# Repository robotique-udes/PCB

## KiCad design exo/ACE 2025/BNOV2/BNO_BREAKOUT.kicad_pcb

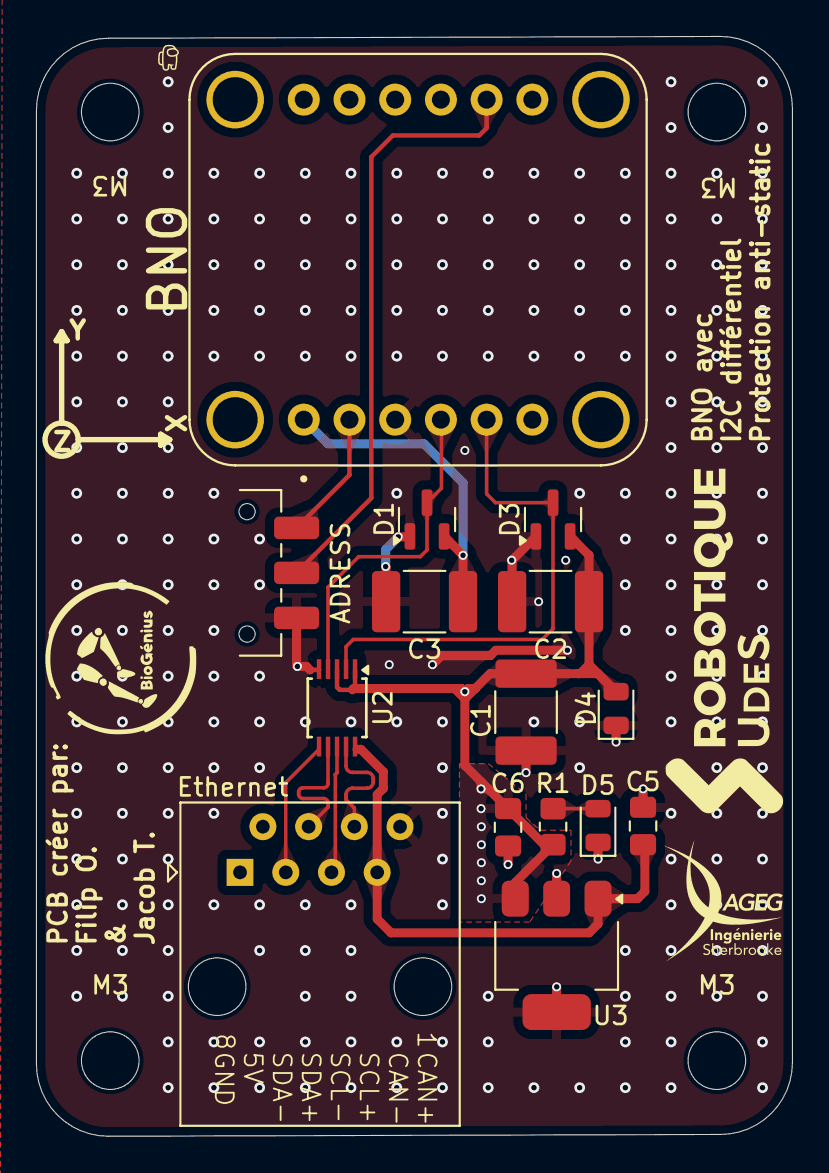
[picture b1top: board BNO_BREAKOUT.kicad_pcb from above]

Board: 2 copper layers, 42.0 x 61.1 mm, 17 parts (0 on the bottom side), 12 nets.

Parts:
ADRESS: SW_SPDT; SW_SPDT_CK_JS102011SAQN
BNO: 4754; MODULE_4754
C1: 4.7uF; C_1812_4532Metric_Pad1.57x3.40mm_HandSolder
C2, C3: 1n; C_1812_4532Metric_Pad1.57x3.40mm_HandSolder
C5, C6: 4,7µF; C_0805_2012Metric_Pad1.18x1.45mm_HandSolder
D1, D3: BAV99; SOT-23
D4: D_TVS_Filled; D_0805_2012Metric
D5: Green_power; D_0805_2012Metric
Ethernet: RJ45; RJ45_Amphenol_54602-x08_Horizontal
M3, M3#2: MountingHole_3.2mm_M3
R1: 330; R_0805_2012Metric_Pad1.20x1.40mm_HandSolder
U2: PCA9615DPZ; TSSOP-10_3x3mm_P0.5mm
U3: AP7361C-33E; SOT-223-3_TabPin2

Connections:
/3V3: BNO.JP1_1 (VIN), C1.1, C2.1, C3.1, C6.2, D1.2 (A), D3.2 (A), D4.2 (A2), R1.1, U2.1 (VDD(A)), U2.3 (EN), U3.3 (VO)
/5V: C5.2, Ethernet.7, U2.10 (VDD(B)), U3.1 (VI)
/SCL: BNO.JP1_4 (SCL), D1.3 (K), U2.4 (SCL)
/SCL+: Ethernet.3, U2.6 (DSCLM)
/SCL-: Ethernet.4, U2.7 (DSCLP)
/SDA: BNO.JP1_5 (SDA), D3.3 (K), U2.2 (SDA)
/SDA+: Ethernet.5, U2.8 (DSDAP)
/SDA-: Ethernet.6, U2.9 (DSDAM)
GND: ADRESS.3 (C), BNO.JP1_3 (GND), C1.2, C2.2, C3.2, C5.1, C6.1, D1.1 (K), D3.1 (K), D4.1 (A1), D5.1 (K), Ethernet.8, U2.5 (VSS), U3.2 (GND)
unnamed: D5.2 (A), R1.2
unnamed: ADRESS.1 (A), BNO.JP1_2 (3VO)
unnamed: ADRESS.2 (B), BNO.JP2_5 (DI)

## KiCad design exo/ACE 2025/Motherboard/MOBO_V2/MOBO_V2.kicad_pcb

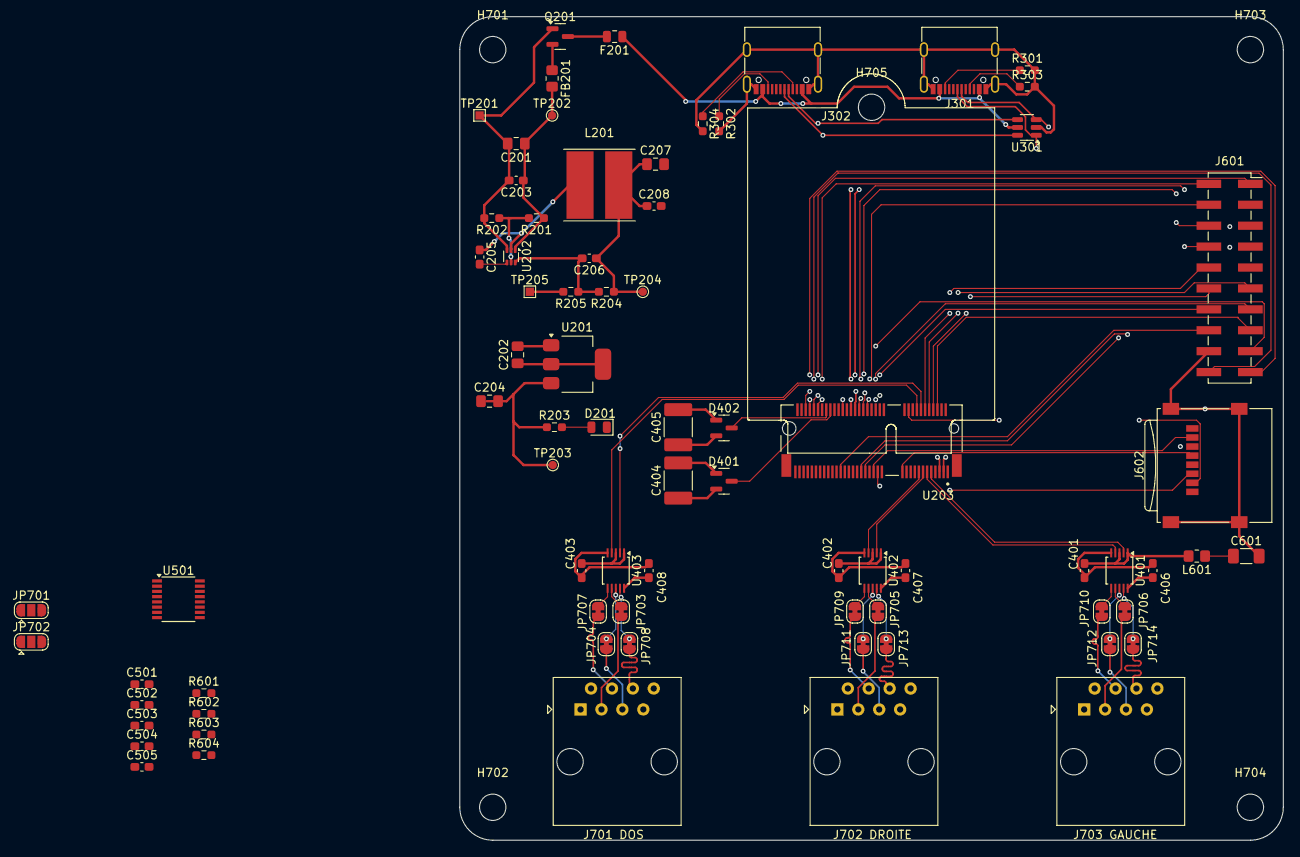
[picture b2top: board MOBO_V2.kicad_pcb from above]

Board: 4 copper layers, 100.0 x 100.0 mm, 82 parts (0 on the bottom side), 89 nets.

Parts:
C201: 10µF; C_0805_2012Metric_Pad1.18x1.45mm_HandSolder
C202, C204: 4,7µF; C_0805_2012Metric_Pad1.18x1.45mm_HandSolder
C203, C205, C208: 0,1µF; C_0603_1608Metric_Pad1.08x0.95mm_HandSolder
C206: 33pF; C_0603_1608Metric_Pad1.08x0.95mm_HandSolder
C207: 22µF; C_0805_2012Metric_Pad1.18x1.45mm_HandSolder
C401, C402, C403, C406, C407, C408: 1nF; C_0603_1608Metric_Pad1.08x0.95mm_HandSolder
C404, C405: 1n; C_1812_4532Metric_Pad1.57x3.40mm_HandSolder
C501, C502, C503, C504, C505: 0.1µF; C_0603_1608Metric_Pad1.08x0.95mm_HandSolder
C601: 47µF; C_1206_3216Metric_Pad1.33x1.80mm_HandSolder
D201: Green_power; D_0805_2012Metric
D401, D402: BAV99; SOT-23
F201: SMD0805B110TF; Fuse_0805_2012Metric
FB201: 600 @ 100MHz; R_0805_2012Metric_Pad1.20x1.40mm_HandSolder
H701, H702, H703, H704: MountingHole; MountingHole_3.2mm_M3
H705: MountingHole SoM; MountingHole_3.2mm_M3
J301: USB_C_UART; USB_C_Receptacle_G-Switch_GT-USB-7010ASV
J302: USB_C_DEBUG; USB_C_Receptacle_G-Switch_GT-USB-7010ASV
J601: Conn_02x10_Counter_Clockwise; PinSocket_2x10_P2.54mm_Vertical_SMD
J602: Micro_SD_Card; microSD_HC_Wuerth_693072010801
J701 DOS, J702 DROITE, J703 GAUCHE: RJ45; RJ45_Amphenol_54602-x08_Horizontal
JP701, JP702: SolderJumper_3_Open; SolderJumper-3_P1.3mm_Open_RoundedPad1.0x1.5mm
JP703, JP704, JP705, JP706, JP707, JP708, JP709, JP710, JP711, JP712, JP713, JP714: SolderJumper_2_Bridged; SolderJumper-2_P1.3mm_Bridged_RoundedPad1.0x1.5mm
L201: 3,3µH 20mOhm; L_TDK_VLP8040
L601: 600R; R_0805_2012Metric_Pad1.20x1.40mm_HandSolder
Q201: AO3401A; SOT-23
R201: 100k; R_0603_1608Metric_Pad0.98x0.95mm_HandSolder
R202: 28k; R_0603_1608Metric_Pad0.98x0.95mm_HandSolder
R203: 330; R_0603_1608Metric_Pad0.98x0.95mm_HandSolder
R204: 158k; R_0603_1608Metric_Pad0.98x0.95mm_HandSolder
R205: 30k; R_0603_1608Metric_Pad0.98x0.95mm_HandSolder
R301, R302, R303, R304: 5.1k; R_0603_1608Metric_Pad0.98x0.95mm_HandSolder
R601, R602, R603, R604: 47k; R_0603_1608Metric_Pad0.98x0.95mm_HandSolder
TP201: TP_GND_IN; TestPoint_Pad_1.0x1.0mm
TP202: TP_VIN; TestPoint_Pad_D1.0mm
TP203: TP_3v3; TestPoint_Pad_D1.0mm
TP204: TP_5V; TestPoint_Pad_D1.0mm
TP205: TP_GND_OUT; TestPoint_Pad_1.0x1.0mm
U201: AP7361C-33E; SOT-223-3_TabPin2
U202: TPS562242DRLR; SOT-563
U203: AMPHENOL_MDT320E01001
U301: SRV05-4; SOT-23-6
U401, U402, U403: PCA9615DP; TSSOP-10_3x3mm_P0.5mm
U501: MAX3221; SSOP-16_3.9x4.9mm_P0.635mm

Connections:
/CAN/CAN_N: JP702.3 (B), U203.73 (CAN_L_MCP2515)
/CAN/CAN_P: JP701.3 (B), U203.71 (CAN_H_MCP2515)
/CAN/GPIO17_U1_TXD: U203.32 (UART_RX), U501.11 (DIN)
/CAN/GPIO18_U1_RXD: U203.22 (UART_TX), U501.9 (ROUT)
/CAN/RS232_RX: JP702.1 (A), U501.8 (RIN)
/CAN/RS232_TX: JP701.1 (A), U501.13 (DOUT)
/Connecteurs/CAN+: J701 DOS.1, J702 DROITE.1, J703 GAUCHE.1, JP701.2 (C)
/Connecteurs/CAN-: J701 DOS.2, J702 DROITE.2, J703 GAUCHE.2, JP702.2 (C)
/Connecteurs/D.SCL1: JP705.1 (A), U402.7 (DSCLP)
/Connecteurs/D.SCL2: JP709.1 (A), U402.6 (DSCLM)
/Connecteurs/D.SDA1: JP711.1 (A), U402.8 (DSDAP)
/Connecteurs/D.SDA2: JP713.1 (A), U402.9 (DSDAM)
/Connecteurs/DOS.SCL1: JP703.1 (A), U403.7 (DSCLP)
/Connecteurs/DOS.SCL2: JP707.1 (A), U403.6 (DSCLM)
/Connecteurs/DOS.SDA1: JP704.1 (A), U403.8 (DSDAP)
/Connecteurs/DOS.SDA2: JP708.1 (A), U403.9 (DSDAM)
/Connecteurs/DOS_SCL+: J701 DOS.3, JP703.2 (B)
/Connecteurs/DOS_SCL-: J701 DOS.4, JP707.2 (B)
/Connecteurs/DOS_SDA+: J701 DOS.5, JP704.2 (B)
/Connecteurs/DOS_SDA-: J701 DOS.6, JP708.2 (B)
/Connecteurs/D_SCL+: J702 DROITE.3, JP705.2 (B)
/Connecteurs/D_SCL-: J702 DROITE.4, JP709.2 (B)
/Connecteurs/D_SDA+: J702 DROITE.5, JP711.2 (B)
/Connecteurs/D_SDA-: J702 DROITE.6, JP713.2 (B)
/Connecteurs/G.SCL1: JP706.1 (A), U401.7 (DSCLP)
/Connecteurs/G.SCL2: JP710.1 (A), U401.6 (DSCLM)
/Connecteurs/G.SDA1: JP712.1 (A), U401.8 (DSDAP)
/Connecteurs/G.SDA2: JP714.1 (A), U401.9 (DSDAM)
/Connecteurs/G_SCL+: J703 GAUCHE.3, JP706.2 (B)
/Connecteurs/G_SCL-: J703 GAUCHE.4, JP710.2 (B)
/Connecteurs/G_SDA+: J703 GAUCHE.5, JP712.2 (B)
/Connecteurs/G_SDA-: J703 GAUCHE.6, JP714.2 (B)
/ESP32_SD_EXTRA/CS_1: J602.2 (DAT3/CD), U203.20 (SPI_CS_5)
/ESP32_SD_EXTRA/CS_2: R604.2, U203.21 (SPI_CS_6)
/ESP32_SD_EXTRA/GPIO15: J601.4, U203.40 (GPIO15)
/ESP32_SD_EXTRA/GPIO16: J601.5, U203.41 (GPIO16)
/ESP32_SD_EXTRA/GPIO26: J601.6, U203.42 (GPIO26)
/ESP32_SD_EXTRA/GPIO33: J601.7, U203.43 (GPIO33)
/ESP32_SD_EXTRA/GPIO34: J601.8, U203.44 (GPIO34)
/ESP32_SD_EXTRA/GPIO38_ADDRESSABLE_LED: J601.15, U203.6 (GPIO38&LED)
/ESP32_SD_EXTRA/GPIO45: J601.17, U203.52 (GPIO45)
/ESP32_SD_EXTRA/GPIO46: J601.16, U203.53 (GPIO46)
/ESP32_SD_EXTRA/GPIO47: J601.14, U203.34 (RST_OTHER)
/ESP32_SD_EXTRA/GPIO48/CAN_INT: J601.13, U203.36 (GPIO48)
/ESP32_SD_EXTRA/I2S_BCLK: J601.12, U203.8 (I2S_BCLK)
/ESP32_SD_EXTRA/I2S_DIN/DOUT: J601.10, U203.12 (I2S_DIN/DOUT)
/ESP32_SD_EXTRA/I2S_WS: J601.11, U203.10 (I2S_WS)
/ESP32_SD_EXTRA/PWM_1: J601.2, U203.64 (PWM_1_PCA)
/ESP32_SD_EXTRA/PWM_2: J601.1, U203.66 (PWM_2_PCA)
/ESP32_SD_EXTRA/PWM_3: J601.20, U203.68 (PWM_3_PCA)
/ESP32_SD_EXTRA/PWM_4: J601.19, U203.70 (PWM_4_PCA)
/ESP32_SD_EXTRA/SPI_CLK_ESP32: J602.5 (CLK), R603.2, U203.23 (SPI_CLK)
/ESP32_SD_EXTRA/SPI_MISO_ESP32: J602.7 (DAT0), R601.2, U203.37 (SPI_MISO)
/ESP32_SD_EXTRA/SPI_MOSI_ESP32: J602.3 (CMD), R602.2, U203.35 (SPI_MOSI)
/I2C_w_Protection/I2C_SCL_0_TCA: U203.11 (I2C_SCL_1_TCA), U401.4 (SCL)
/I2C_w_Protection/I2C_SCL_1_TCA: U203.15 (I2C_SCL_2_TCA), U402.4 (SCL)
/I2C_w_Protection/I2C_SCL_2_TCA: U203.16 (I2C_SCL_3_TCA), U403.4 (SCL)
/I2C_w_Protection/I2C_SDA_0_TCA: U203.9 (I2C_SDA_1_TCA), U401.2 (SDA)
/I2C_w_Protection/I2C_SDA_1_TCA: U203.13 (I2C_SDA_2_TCA), U402.2 (SDA)
/I2C_w_Protection/I2C_SDA_2_TCA: U203.14 (I2C_SDA_3_TCA), U403.2 (SDA)
/USB/DEBUG_D+: J302.A6 (D+), J302.B6 (D+), U203.48 (USB_DEBUG_D+), U301.6 (IO4)
/USB/DEBUG_D-: J302.A7 (D-), J302.B7 (D-), U203.46 (USB_DEBUG_D-), U301.4 (IO3)
/USB/FT231_D+: J301.A6 (D+), J301.B6 (D+), U203.3 (USB_D+_FT231), U301.3 (IO2)
/USB/FT231_D-: J301.A7 (D-), J301.B7 (D-), U203.5 (USB_D-_FT231), U301.1 (IO1)
GND: C201.2, C202.1, C203.2, C204.1, C207.2, C208.2, C401.2, C402.2, C403.2, C404.2, C405.2, C406.2, C407.2, C408.2, C503.2, C504.2, C505.2, C601.2, D201.1 (K), D401.1 (K), D402.1 (K), J301.A1 (GND), J301.A12 (GND), J301.B1 (GND), J301.B12 (GND), J301.S1 (SHIELD), J302.A1 (GND), J302.A12 (GND), J302.B1 (GND), J302.B12 (GND), J302.S1 (SHIELD), J601.18, J602.6 (VSS), J602.9 (SHIELD), J701 DOS.8, J702 DROITE.8, J703 GAUCHE.8, Q201.1 (G), R202.2, R205.2, R301.2, R302.2, R303.2, R304.2, TP201.1, TP205.1, U201.2 (GND), U202.3 (GND), U203.1 (GND), U203.7 (GND), U203.18 (GND), U203.33 (GND), U203.38 (GND), U203.39 (GND), U203.45 (GND), U203.51 (GND), U203.55 (GND), U203.57 (GND), U203.62 (GND), U203.63 (GND), U203.69 (GND), U203.75 (GND), U301.2 (VN), U401.5 (V_{SS}), U402.5 (V_{SS}), U403.5 (V_{SS}), U501.1 (~EN), U501.14 (GND)
I2C_SCL_ESP32: D402.3 (K), U203.60 (I2C_SCL_ESP32)
I2C_SDA_ESP32: D401.3 (K), U203.58 (I2C_SDA_ESP32)
unnamed: D201.2 (A), R203.2
unnamed: J301.A5 (CC1), R303.1
unnamed: J301.B5 (CC2), R301.1
unnamed: J302.A5 (CC1), R304.1
unnamed: J302.B5 (CC2), R302.1
unnamed: C601.1, J602.4 (VDD), L601.1
unnamed: F201.2, Q201.3 (D)
unnamed: FB201.1, Q201.2 (S)
unnamed: R201.2, R202.1, U202.5 (EN)
unnamed: C205.1, L201.1, U202.2 (SW)
unnamed: C205.2, U202.4 (VBST)
unnamed: C206.2, R204.2, R205.1, U202.6 (VFB)
unnamed: C501.1, U501.2 (C1+)
unnamed: C501.2, U501.4 (C1-)
unnamed: C502.1, U501.5 (C2+)
unnamed: C502.2, U501.6 (C2-)
unnamed: C504.1, U501.3 (V+)
unnamed: C505.1, U501.7 (V-)
VBUS: F201.1, J301.A4 (VBUS), J301.A9 (VBUS), J301.B4 (VBUS), J301.B9 (VBUS), J302.A4 (VBUS), J302.A9 (VBUS), J302.B4 (VBUS), J302.B9 (VBUS), U301.5 (VP)
VIN_PROTECTION: C201.1, C203.1, FB201.2, R201.1, TP202.1, U202.1 (VIN)
Vcc_3V3: C204.2, C401.1, C402.1, C403.1, C404.1, C405.1, C503.1, D401.2 (A), D402.2 (A), J601.3, J601.9, L601.2, R203.1, R601.1, R602.1, R603.1, R604.1, TP203.1, U201.3 (VO), U203.2 (Vcc_3v3), U203.4 (Vcc_3v3), U203.72 (Vcc_3v3), U203.74 (Vcc_3v3), U401.1 (V_{DD(A)}), U401.3 (EN), U402.1 (V_{DD(A)}), U402.3 (EN), U403.1 (V_{DD(A)}), U403.3 (EN), U501.12 (FORCEON), U501.15 (VCC), U501.16 (~FORCEOFF)
Vcc_5V: C202.2, C206.1, C207.1, C208.1, C406.1, C407.1, C408.1, J701 DOS.7, J702 DROITE.7, J703 GAUCHE.7, L201.2, R204.1, TP204.1, U201.1 (VI), U203.50 (Vcc_5V), U401.10 (V_{DD(B)}), U402.10 (V_{DD(B)}), U403.10 (V_{DD(B)})

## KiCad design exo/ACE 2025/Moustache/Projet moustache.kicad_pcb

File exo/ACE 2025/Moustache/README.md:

2025 Exo Moustache
The Moustache is a small pcb made to receive I2C in differencial, CAN and power by an ethernet port and distributed trought 6 other ethernet port to connect the captors and motors

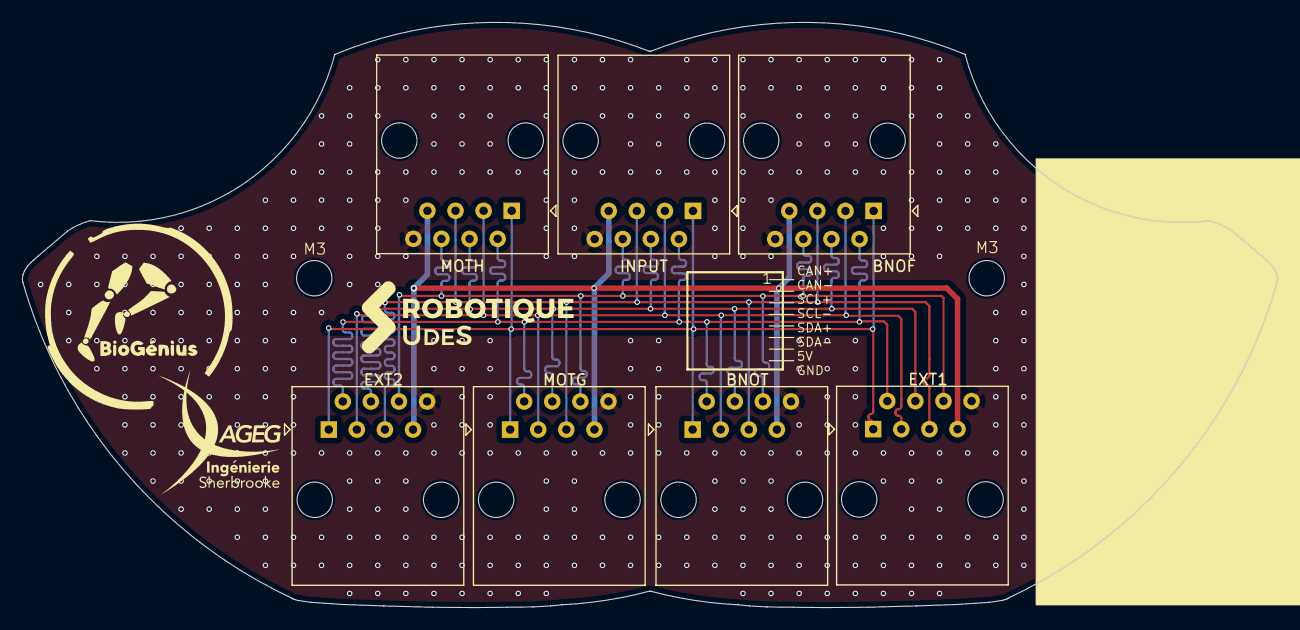
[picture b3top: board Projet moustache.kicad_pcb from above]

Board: 2 copper layers, 113.5 x 52.9 mm, 9 parts (0 on the bottom side), 8 nets.

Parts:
BNOF: RJ45; RJ45_Amphenol_54602-x08_Horizontal
BNOT: RJ45; RJ45_Amphenol_54602-x08_Horizontal
EXT1, EXT2: RJ45; RJ45_Amphenol_54602-x08_Horizontal
H1, H2: MountingHole; MountingHole_3.2mm_M3
INPUT: RJ45; RJ45_Amphenol_54602-x08_Horizontal
MOTG: RJ45; RJ45_Amphenol_54602-x08_Horizontal
MOTH: RJ45; RJ45_Amphenol_54602-x08_Horizontal

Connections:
+5V: BNOF.7, BNOT.7, EXT1.7, EXT2.7, INPUT.7, MOTG.7, MOTH.7
/CAN+: BNOF.1, BNOT.1, EXT1.1, EXT2.1, INPUT.1, MOTG.1, MOTH.1
/CAN-: BNOF.2, BNOT.2, EXT1.2, EXT2.2, INPUT.2, MOTG.2, MOTH.2
/SCL+: BNOF.3, BNOT.3, EXT1.3, EXT2.3, INPUT.3, MOTG.3, MOTH.3
/SCL-: BNOF.4, BNOT.4, EXT1.4, EXT2.4, INPUT.4, MOTG.4, MOTH.4
/SDA+: BNOF.5, BNOT.5, EXT1.5, EXT2.5, INPUT.5, MOTG.5, MOTH.5
/SDA-: BNOF.6, BNOT.6, EXT1.6, EXT2.6, INPUT.6, MOTG.6, MOTH.6
GND: BNOF.8, BNOT.8, EXT1.8, EXT2.8, INPUT.8, MOTG.8, MOTH.8

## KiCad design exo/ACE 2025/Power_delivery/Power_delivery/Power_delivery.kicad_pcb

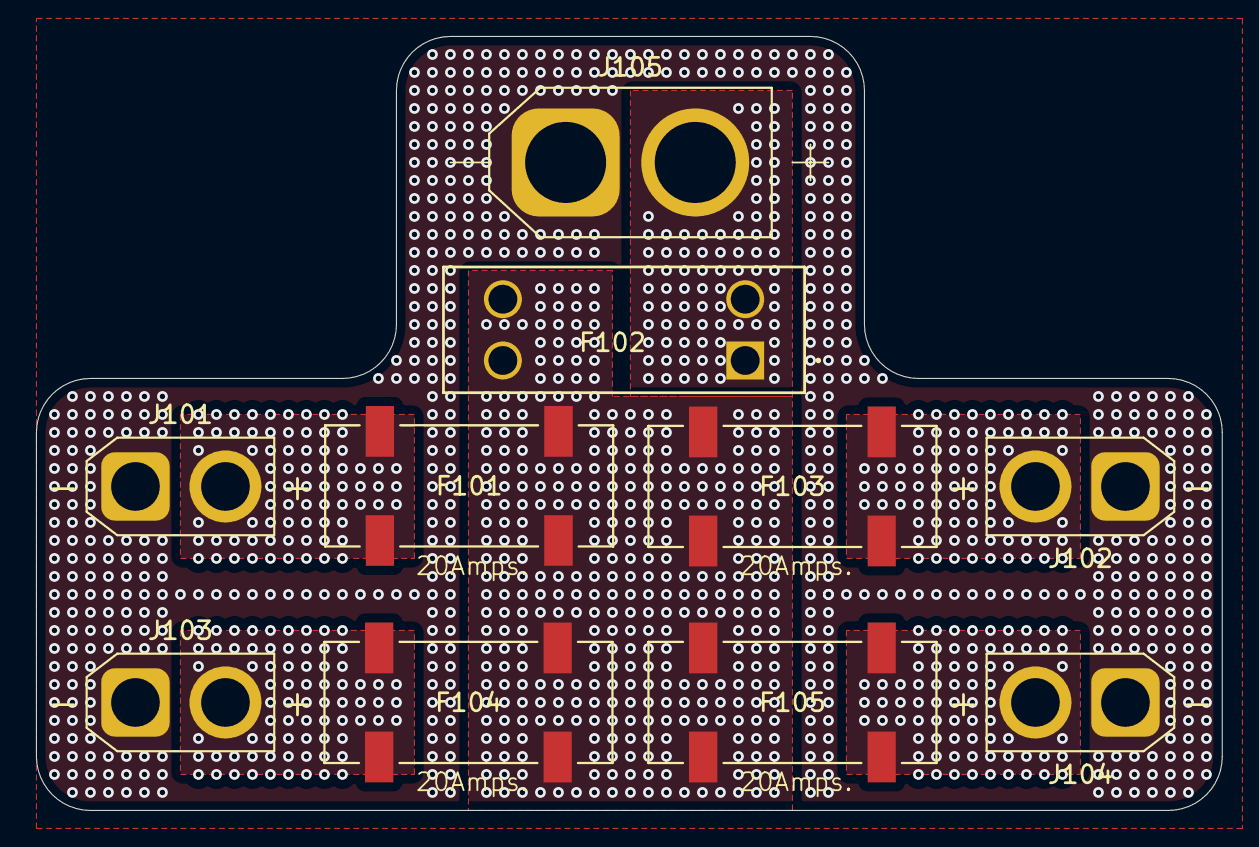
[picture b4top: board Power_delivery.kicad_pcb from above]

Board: 4 copper layers, 65.9 x 43.0 mm, 10 parts (0 on the bottom side), 7 nets, no tracks yet.

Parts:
F101, F103, F104, F105: 3588-20; FUSE_3588-20
F102: 3557-15; 3557-15_KEY
J101, J102, J103, J104: XT30U; AMASS_XT30U-F_1x02_P5.0mm_Vertical
J105: XT60; AMASS_XT60-F_1x02_P7.20mm_Vertical

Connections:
/48V: F102.1, F102.2, J105.2
GND: J101.1, J102.1, J103.1, J104.1, J105.1
unnamed: F101.1_1, F101.1_2, F102.3, F102.4, F103.1_1, F103.1_2, F104.1_1, F104.1_2, F105.1_1, F105.1_2
unnamed: F101.2_1, F101.2_2, J101.2
unnamed: F103.2_1, F103.2_2, J102.2
unnamed: F104.2_1, F104.2_2, J103.2
unnamed: F105.2_1, F105.2_2, J104.2

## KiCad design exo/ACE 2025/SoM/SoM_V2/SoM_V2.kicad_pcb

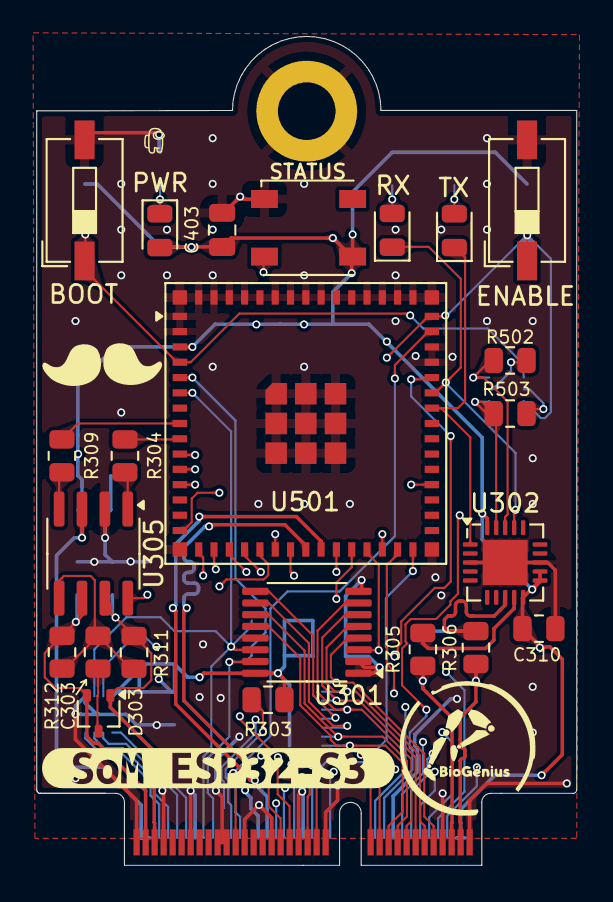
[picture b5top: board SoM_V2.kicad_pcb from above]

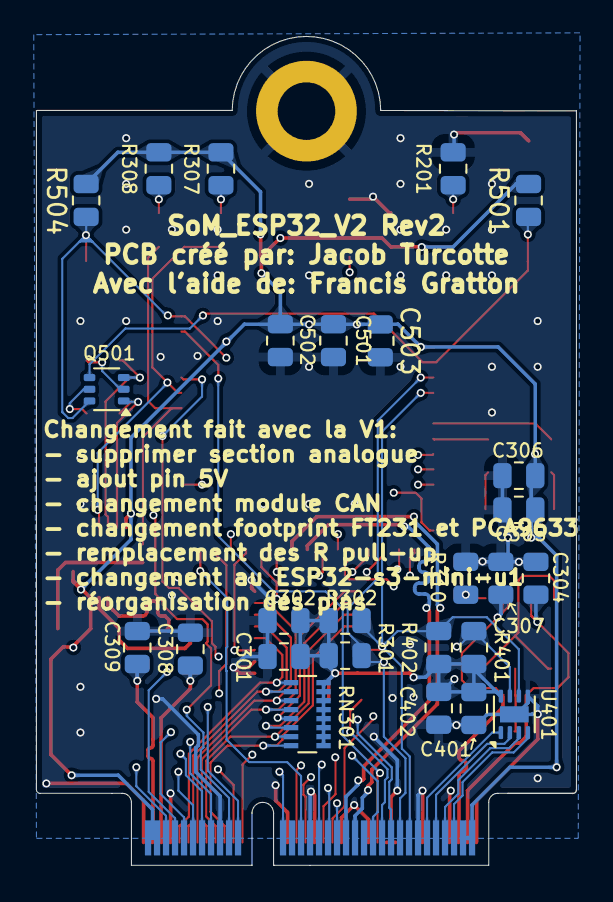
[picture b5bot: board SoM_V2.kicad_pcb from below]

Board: 4 copper layers, 30.0 x 46.1 mm, 51 parts (26 on the bottom side), 62 nets.

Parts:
BOOT: SW_BOOT; SW_DIP_SPSTx01_Slide_6.7x4.1mm_W6.73mm_P2.54mm_LowProfile_J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
C301, C501: 10µF; R_0805_2012Metric
C302, C304, C306, C307, C310, C502: 0.1µF; R_0805_2012Metric
C303, C305, C401, C503: 1µF; R_0805_2012Metric
C308, C309: 47pF; R_0805_2012Metric
C402: 100nF; R_0805_2012Metric
C403: 100n; C_0805_2012Metric
D303: SP0502BAJT; SOT-323_SC-70
ENABLE: SW_CHIP_EN; SW_DIP_SPSTx01_Slide_6.7x4.1mm_W6.73mm_P2.54mm_LowProfile_J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
PWR: GREEN; LED_0805_2012Metric
Q501: MBT3904DW1T1G; SOT-363_SC-70-6
R201, R307, R308: 330; R_0805_2012Metric
R301, R302, R303, R304, R309, R310, R401, R402: 1k; R_0805_2012Metric
R305, R306: 27; R_0805_2012Metric
R311, R312: 60; R_0805_2012Metric
R501, R502, R503, R504: 10k; R_0805_2012Metric
RN301: 1k; R_Array_Convex_8x0602
RX: TX; LED_0805_2012Metric
STATUS: FZ2812-5050; LED_Inolux_IN-PI554FCH_PLCC4_5.0x5.0mm_P3.2mm
TX: RX; LED_0805_2012Metric
U201: NGFF_E
U301: TCA9546APWR; TSSOP-16_4.4x5mm_P0.65mm
U302: FT231XQ; QFN-20-1EP_4x4mm_P0.5mm_EP2.5x2.5mm
U305: SN65HVD230; SOIC-8_3.9x4.9mm_P1.27mm
U401: PCA9633DP1; DFN-8-1EP_2x2mm_P0.5mm_EP0.9x1.6mm
U501: ESP32-S3-MINI-1U; ESP32-S2-MINI-1U
kibuzzard-66E094ED: G***; kibuzzard-66E094ED

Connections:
/Communication/CAN+: C307.2, D303.1 (K), R311.1, U201.71 (CAN_H_MCP2515), U305.7 (CANH)
/Communication/CAN-: C304.1, D303.2 (K), R312.2, U201.73 (CAN_L_MCP2515), U305.6 (CANL)
/Communication/D+: R306.2, U302.8 (USBDP)
/Communication/D-: R305.2, U302.9 (USBDM)
/Communication/DR+: C309.1, R306.1, U201.3 (USB_D+_FT231)
/Communication/DR-: C308.1, R305.1, U201.5 (USB_D-_FT231)
CHIP_EN: ENABLE.1, Q501.6 (C1), R504.1, U201.56 (RESET_ESP32), U501.45 (EN)
CS_1: U201.20 (CS_1), U501.15 (IO11)
CS_2: U201.21 (CS_2), U501.25 (IO21)
DEBUG+: U201.48 (USB_DEBUG_D+), U501.24 (IO20)
DEBUG-: U201.46 (USB_DEBUG_D-), U501.23 (IO19)
DTR: Q501.3 (C2), R502.1, U302.18 (~DTR)
GND: BOOT.2, C301.2, C302.2, C304.2, C305.2, C306.2, C307.1, C308.2, C309.2, C310.2, C401.2, C402.2, C403.2, C501.2, C502.2, C503.2, ENABLE.2, R201.2, R310.1, STATUS.1 (VSS), U201.1 (GND), U201.7 (GND), U201.18 (GND), U201.33 (GND), U201.38 (GND), U201.39 (GND), U201.45 (GND), U201.51 (GND), U201.55 (GND), U201.57 (GND), U201.62 (GND), U201.63 (GND), U201.69 (GND), U201.75 (GND), U301.1 (A0), U301.2 (A1), U301.8 (GND), U301.13 (A2), U302.3 (GND), U302.13 (GND), U302.21 (GND), U305.2 (GND), U401.5 (GND), U501.1 (GND), U501.2 (GND), U501.42 (GND), U501.43 (GND), U501.46 (GND), U501.47 (GND), U501.48 (GND), U501.49 (GND), U501.50 (GND), U501.51 (GND), U501.52 (GND), U501.53 (GND), U501.54 (GND), U501.55 (GND), U501.56 (GND), U501.57 (GND), U501.58 (GND), U501.59 (GND), U501.60 (GND), U501.61 (GND), U501.62 (GND), U501.63 (GND), U501.64 (GND), U501.65 (GND)
GPIO0_BOOT: BOOT.1, Q501.4 (E2), R501.1, U501.4 (IO0)
GPIO4/RXD: R309.1, U501.8 (IO4)
GPIO5/TXD: R304.1, U501.9 (IO5)
GPIO15: U201.40 (GPIO15), U501.19 (IO15)
GPIO16: U201.41 (GPIO16), U501.20 (IO16)
GPIO17_U1_TXD: U201.22 (UART_TX), U501.21 (IO17)
GPIO18_U1_RXD: U201.32 (UART_RX), U501.22 (IO18)
GPIO26: U201.42 (GPIO26), U501.26 (IO26)
GPIO33: U201.43 (GPIO33), U501.28 (IO33)
GPIO34: U201.44 (GPIO34), U501.29 (IO34)
GPIO38_ADDRESSABLE_LED: STATUS.2 (DIN), U201.6 (GPIO38&LED), U501.34 (IO38)
GPIO45: U201.52 (GPIO45), U501.41 (IO45)
GPIO46: U201.53 (GPIO46), U501.44 (IO46)
GPIO48/CAN_INT: U201.36 (GPIO48), U501.30 (IO48)
I2C_SCL_0_TCA: RN301.2 (R2.1), U201.11 (I2C_SCL_1_TCA), U301.5 (SC0)
I2C_SCL_1_TCA: RN301.4 (R4.1), U201.15 (I2C_SCL_2_TCA), U301.7 (SC1)
I2C_SCL_2_TCA: RN301.6 (R6.1), U201.16 (I2C_SCL_3_TCA), U301.10 (SC2)
I2C_SCL_3_TCA: RN301.8 (R8.1), U201.19 (I2C_SCL_4_TCA), U301.12 (SC3)
I2C_SCL_ESP32: R302.2, R402.2, U201.60 (I2C_SCL_ESP32), U301.14 (SCL), U401.6 (SCL6), U501.6 (IO2)
I2C_SDA_0_TCA: RN301.1 (R1.1), U201.9 (I2C_SDA_1_TCA), U301.4 (SD0)
I2C_SDA_1_TCA: RN301.3 (R3.1), U201.13 (I2C_SDA_2_TCA), U301.6 (SD1)
I2C_SDA_2_TCA: RN301.5 (R5.1), U201.14 (I2C_SDA_3_TCA), U301.9 (SD2)
I2C_SDA_3_TCA: RN301.7 (R7.1), U201.17 (I2C_SDA_4_TCA), U301.11 (SD3)
I2C_SDA_ESP32: R301.2, R401.2, U201.58 (I2C_SDA_ESP32), U301.15 (SDA), U401.7 (SDA), U501.5 (IO1)
I2S_BCLK: U201.8 (I2S_BCLK), U501.16 (IO12)
I2S_DIN/DOUT: U201.12 (I2S_DIN/DOUT), U501.18 (IO14)
I2S_WS: U201.10 (I2S_WS), U501.17 (IO13)
unnamed: PWR.1 (K), R201.1
unnamed: R307.1, RX.2 (A)
unnamed: R308.1, TX.2 (A)
unnamed: C303.2, D303.3 (A)
unnamed: Q501.2 (B1), R502.2
unnamed: Q501.5 (B2), R503.2
unnamed: U201.64 (PWM_1_PCA), U401.1 (PWM1)
unnamed: U201.66 (PWM_2_PCA), U401.2 (PWM2)
unnamed: U201.68 (PWM_3_PCA), U401.3 (PWM3)
unnamed: U201.70 (PWM_4_PCA), U401.4 (PWM4)
unnamed: R304.2, U305.1 (D)
unnamed: R309.2, U305.4 (R)
unnamed: R310.2, U305.8 (Rs)
RESET_OTHERS: R303.2, U201.54 (RESET_AUTRES), U301.3 (RESET_N), U501.27 (IO47)
RTS: Q501.1 (E1), R503.1, U302.19 (~RTS)
SPI_CLK_ESP32: U201.23 (SPI_CLK), U501.10 (IO6)
SPI_MISO_ESP32: U201.37 (SPI_MISO), U501.12 (IO8)
SPI_MOSI_ESP32: U201.35 (SPI_MOSI), U501.11 (IO7)
U0RXD: RX.1 (K), U302.17 (TXD), U501.40 (RXD0)
U0TXD: TX.1 (K), U302.1 (RXD), U501.39 (TXD0)
Vcc_3V3: C301.1, C302.1, C305.1, C306.1, C310.1, C401.1, C402.1, C403.1, C501.1, C502.1, C503.1, PWR.2 (A), R301.1, R302.1, R303.1, R307.2, R308.2, R401.1, R402.1, R501.2, R504.2, RN301.9 (R8.2), RN301.10 (R7.2), RN301.11 (R6.2), RN301.12 (R5.2), RN301.13 (R4.2), RN301.14 (R3.2), RN301.15 (R2.2), RN301.16 (R1.2), STATUS.3 (VDD), U201.2 (Vcc_3v3), U201.4 (Vcc_3v3), U201.72 (Vcc_3v3), U201.74 (Vcc_3v3), U301.16 (VCC), U302.10 (3V3OUT), U302.11 (~RESET), U302.12 (VCC), U302.20 (VCCIO), U305.3 (VCC), U401.8 (VCC), U501.3 (3V3)
Vref_CAN: C303.1, R311.2, R312.1, U305.5 (Vref)

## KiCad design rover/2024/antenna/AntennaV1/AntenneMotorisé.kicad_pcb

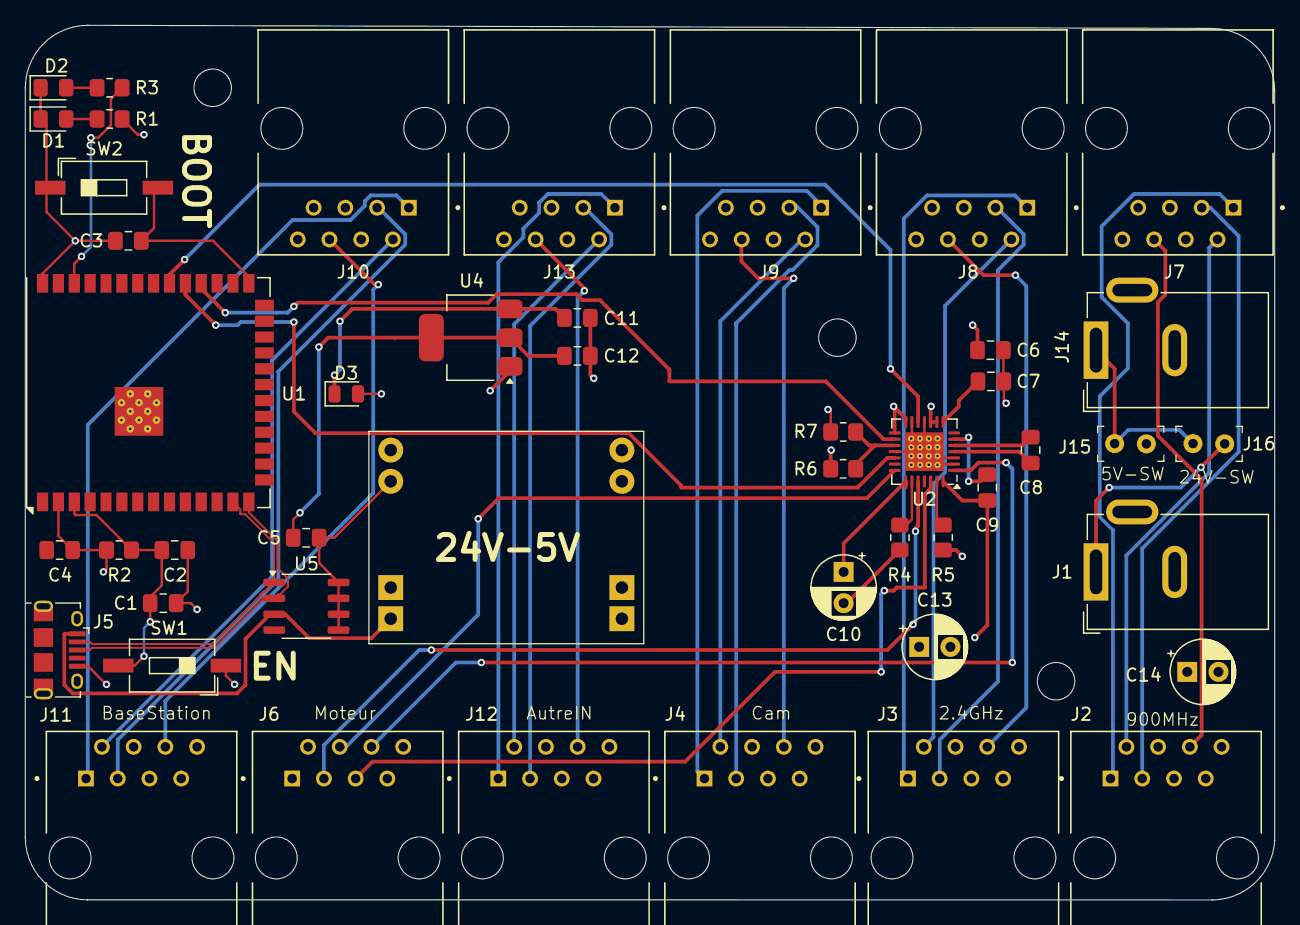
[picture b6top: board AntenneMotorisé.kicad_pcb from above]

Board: 4 copper layers, 100.0 x 70.0 mm, 47 parts (1 on the bottom side), 47 nets.

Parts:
C1, C3, C5: 100nF; C_0805_2012Metric_Pad1.18x1.45mm_HandSolder
C2: 1uF; C_0805_2012Metric_Pad1.18x1.45mm_HandSolder
C4: 22uF; C_0805_2012Metric_Pad1.18x1.45mm_HandSolder
C6, C7: 0.22uF; C_0805_2012Metric_Pad1.18x1.45mm_HandSolder
C8, C9: 0.1uF; C_0805_2012Metric_Pad1.18x1.45mm_HandSolder
C10, C13, C14: 100uF; CP_Radial_D5.0mm_P2.50mm
C11: 10u; C_0805_2012Metric_Pad1.18x1.45mm_HandSolder
C12: 22u; C_0805_2012Metric_Pad1.18x1.45mm_HandSolder
D1: R; LED_0805_2012Metric_Pad1.15x1.40mm_HandSolder
D2: B; LED_0805_2012Metric_Pad1.15x1.40mm_HandSolder
D3: 1N4004; D_0805_2012Metric
J1, J14: Barrel_Jack; BarrelJack_GCT_DCJ200-10-A_Horizontal
J2: POE900; AMPHENOL_54601-908WPLF
J3: POE2.4; AMPHENOL_54601-908WPLF
J4: CameraIN; AMPHENOL_54601-908WPLF
J5: BaseStation; AMPHENOL_54601-908WPLF
J6: Moteur; AMPHENOL_54601-908WPLF
J7: LAN900; AMPHENOL_54601-908WPLF
J8: LAN2.4; AMPHENOL_54601-908WPLF
J9: LANCamera; AMPHENOL_54601-908WPLF
J10: SwitchOut; AMPHENOL_54601-908WPLF
J11: USB_B_Micro; USB_Micro-B_Amphenol_10118194_Horizontal
J12: Eth4IN; AMPHENOL_54601-908WPLF
J13: LAN4; AMPHENOL_54601-908WPLF
J15, J16: M20-9990246; PinHeader_1x2_P2.54mm
R1, R3: 330; R_0805_2012Metric_Pad1.20x1.40mm_HandSolder
R2: 10K TBV; R_0805_2012Metric_Pad1.20x1.40mm_HandSolder
R4, R5: 0.05; R_0805_2012Metric_Pad1.20x1.40mm_HandSolder
R6: 12k; R_0805_2012Metric_Pad1.20x1.40mm_HandSolder
R7: 1k; R_0805_2012Metric_Pad1.20x1.40mm_HandSolder
SW1, SW2: TS09-63-25-WT-160-SMT-TR; SW_DIP_SPSTx01_Slide_6.7x4.1mm_W8.61mm_P2.54mm_LowProfile
U1: ESP32-S3-WROOM-1
U2: A4988-Stepper Driver; QFN-28-1EP_5x5mm_P0.5mm_EP3.1x3.1mm_ThermalVias
U3: MP1584EN-Buck Converter; Buck_7V-24V_5V
U4: AMS1117-3.3; SOT-223-3_TabPin2
U5: SO-8_3.9x4.9mm_P1.27mm

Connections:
+3.3V: C4.1, C5.1, C12.1, R1.1, R2.1, U1.2 (3V3), U4.2 (VO)
+5V: C6.1, D3.2 (A), J11.1 (VBUS), J15.1, R6.1, U2.9 (MS1), U2.10 (MS2), U2.14 (~SLEEP), U2.15 (VDD), U3.5 (Vout+), U3.6 (Vout+), U5.3
+24V: C9.2, C10.1, C13.1, C14.1, J1.1, J2.4, J2.5, J3.4, J3.5, J16.1, U2.22 (VBB1), U2.28 (VBB2), U3.1 (Vin+), U3.2 (Vin+)
DIRPIN: U1.31 (IO38), U2.19 (DIR)
EN_PB: C1.2, C2.1, R2.2, SW1.2, U1.3 (EN)
GND: C1.1, C2.2, C3.1, C4.2, C5.2, C6.2, C7.2, C10.2, C11.2, C12.2, C13.2, C14.2, D1.1 (K), D2.1 (K), J1.2, J2.7, J2.8, J3.7, J3.8, J11.5 (GND), J11.6 (Shield), J14.2, R4.2, R5.2, R7.2, SW1.1, SW2.1, U1.1 (GND), U1.40 (GND), U1.41 (GND), U2.2 (~ENABLE), U2.3 (GND), U2.11 (MS3), U2.13 (ROSQ), U2.18 (GND), U2.29 (Dissipateur), U3.3 (Vin-), U3.4 (Vin-), U3.7 (Vout-), U3.8 (Vout-), U4.1 (GND), U5.5, U5.6, U5.7, U5.8
GPIO_0: C3.2, SW2.2, U1.27 (IO0)
LED_BUILDIN: R3.2, U1.38 (IO2)
unnamed: D1.2 (A), R1.2
unnamed: D2.2 (A), R3.1
unnamed: C11.1, D3.1 (K), U4.3 (VI)
unnamed: J4.1, J9.1
unnamed: J4.2, J9.2
unnamed: J4.3, J9.3
unnamed: J4.6, J9.6
unnamed: J5.1, J10.1
unnamed: J5.2, J10.2
unnamed: J5.3, J10.3
unnamed: J5.6, J10.6
unnamed: J12.1, J13.1
unnamed: J12.2, J13.2
unnamed: J12.3, J13.3
unnamed: J12.6, J13.6
unnamed: J14.1, J15.2, J16.2
unnamed: C8.1, U2.4 (CP1)
unnamed: C8.2, U2.5 (CP2)
unnamed: C9.1, U2.6 (CVP)
unnamed: R4.1, U2.23 (SENSE1)
unnamed: R5.1, U2.27 (SENSE2)
unnamed: R6.2, R7.1, U2.17 (VREF)
unnamed: C7.1, U2.8 (VREG)
OUT1A: J6.3, U2.24 (OUT1A)
OUT1B: J6.4, U2.21 (OUT1B)
OUT2A: J6.5, U2.26 (OUT2A)
OUT2B: J6.6, U2.1 (OUT2B)
RESETPIN: U1.32 (IO39), U2.12 (~RESET)
Rx+_2.4: J3.3, J8.3
Rx+_900: J2.3, J7.3
Rx-_2.4: J3.6, J8.6
Rx-_900: J2.6, J7.6
STEPPIN: U1.30 (IO37), U2.16 (STEP)
Tx+_2.4: J3.1, J8.1
Tx+_900: J2.1, J7.1
Tx-_2.4: J3.2, J8.2
Tx-_900: J2.2, J7.2
USB_N: J11.2 (D-), U1.13 (IO19), U5.1
USB_P: J11.3 (D+), U1.14 (IO20), U5.2
